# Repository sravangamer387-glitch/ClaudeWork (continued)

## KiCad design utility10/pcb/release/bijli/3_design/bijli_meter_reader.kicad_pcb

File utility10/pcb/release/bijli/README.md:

# Bijli Meter Reader - main board (rev B)

Optical electricity-meter pulse reader: USB-C 5 V powered ATmega328P-AU, sensor-head connector (phototransistor), TM1637 4-digit display connector, reset button, LED.

**Status: engineering release, software-verified only (ERC on the netlist, KiCad DRC, netlist cross-check, SPICE where noted). Not yet built, not reviewed by a second engineer, not certified.**

## Specification
- Board 52 x 38 mm, 2 layers, 1.6 mm FR-4, 1 oz copper, rounded corners R2.5 mm, 4 x M2.5 mounting holes, 2 fiducials.
- Rules used: min track 0.2 mm (power 0.4 mm), min clearance 0.2 mm, via 0.6/0.3 mm, GND pour on both layers, 39 stitching vias.
- Finish: ENIG recommended (HASL lead-free acceptable); green mask, white silk; IPC class 2.
- 23 parts, 17 nets.

## Circuit description
- **Power:** USB-C power-only sink: CC1/CC2 each 5.1 k to GND (R1, R2) so a charger delivers 5 V; 0.5 A PTC fuse F1 (1206) then +5V; SMAJ5.0A TVS D3 on VBUS clamps spikes; 10 uF + 100 nF decoupling.
- **Sensor head:** phototransistor between SIG_H and GND, 10 k pull-up R4 to +5V, 100 ohm series R6 + 100 nF C5 on SIG; SIG falls when the meter LED lights. Firmware adapts its threshold to the observed minimum/maximum (swing must be >= 0.2 V).
- **MCU/display:** ATmega328P-AU at the internal 8 MHz RC, ADC0 reads SIG, TM1637 display module on JST-PH J4 (GND, +5V, DIO, CLK), reset-bill button on PD2, LED on PD7, ISP header.

### Simulation: `sim/bijli_head_results.md`
```
| condition (phototransistor collector current) | SIG voltage | ADC counts (5 V ref) | note |
|---|---|---|---|
| dark / meter LED off, dim room (1 uA) | 4.99 V | 1021 |  |
| indoor ambient light on the head (20 uA) | 4.80 V | 982 |  |
| bright window light (150 uA) | 3.49 V | 713 |  |
| meter LED lit, weak coupling (200 uA) | 2.98 V | 610 |  |
| meter LED lit, typical close clip (1 mA) | 0.20 V | 41 | saturated (collector near 0.2 V) |
| meter LED lit, strong (3 mA) | 0.20 V | 41 | saturated (collector near 0.2 V) |

SIG = 5 V - Ic x (10 k pull-up + 100 ohm), clamped at 0.2 V (saturation). The firmware looks for a swing of more than 40 counts (0.2 V) between its running minimum and maximum, so a lit LED (>= 0.2 mA) against indoor ambient (<= 20 uA) gives a swing of more than 1.5 V. Direct sunlight on the head (> 1 mA) would hide the pulses: use the black clip. Edge speed: 10 k x 100 nF = 1 ms time constant, meter LED pulses are tens of ms.
These phototransistor currents are typical-datasheet assumptions, not measurements of a real meter.
```

## Power
MCU 5 V 8 MHz about 6 mA + display 10-30 mA + LED: under 50 mA, far below the 500 mA default USB limit and the 0.5 A PTC.

## Verification
| Check | Result |
|---|---|
| Electrical rule check on the netlist (own ERC: unconnected pins, single-pin nets, output conflicts, unpowered supplies, symbol/footprint pin match) | 0 errors, 0 warnings |
| KiCad DRC | 0 errors, 0 warnings; unconnected pads: 0 |
| Schematic netlist equals PCB netlist | yes |
| Router failures | 0 |
| 3D STEP export | yes |
| Independent Gerber parse (gerbonara): layers parsed, outline size equals the design | 9 layers, outline [52.1, 38.1] mm, match |

Enclosure (prototype shell for 3D printing): outer 67.2 x 53.2 x 21.0 mm, collision/opening check: pass

## Bill of materials
| Ref | Value | Footprint | Manufacturer part | LCSC # | LCSC status |
|---|---|---|---|---|---|
| U1 | ATmega328P-AU | TQFP-32_7x7mm_P0.8mm | ATMEGA328P-AU | C14877 | verified |
| J1 | USB-C 5V | USB_C_Receptacle_HRO_TYPE-C-31-M-12 | TYPE-C-31-M-12 | C165948 | verified |
| F1 | PTC 500mA | Fuse_1206_3216Metric | Littelfuse 1206L050YR (6 V) | C163512 | verified |
| D3 | SMAJ5.0A | D_SMA | Littelfuse SMAJ5.0A | C83329 | verified |
| J2 | ISP | PinHeader_2x03_P2.54mm_Vertical | HCTL PZ254-2-03-Z-8.5 (ZHOURI C5116479 had only 340 in stock) | C2894964 | verified |
| J3 | Sensor head | JST_PH_B3B-PH-K_1x03_P2.00mm_Vertical | JST B3B-PH-K-S(LF)(SN) | C131339 | verified |
| J4 | TM1637 display | JST_PH_B4B-PH-K_1x04_P2.00mm_Vertical | JST B4B-PH-K-S(LF)(SN) | C131334 | verified |
| SW1 | Reset bill | SW_SPST_B3U-1000P | Omron B3U-1000P | C231329 | verified |
| D1 | Green | LED_0603_1608Metric | Hubei KENTO KT-0603YG yellow-green 570 nm, Vf about 2 V (lights well from 3.3 V with 1 k; the Everlight 19-217 green was out of stock) | C2289 | verified |
| R1 | 5.1k | R_0603_1608Metric | 0603 5.1k 1% | C23186 | verified |
| R2 | 5.1k | R_0603_1608Metric | 0603 5.1k 1% | C23186 | verified |
| R3 | 10k | R_0603_1608Metric | 0603 10k 1% | C25804 | verified |
| R4 | 10k | R_0603_1608Metric | 0603 10k 1% | C25804 | verified |
| R5 | 1k | R_0603_1608Metric | 0603 1k 1% | C21190 | verified |
| R6 | 100 | R_0603_1608Metric | UNI-ROYAL 0603WAF1000T5E | C22775 | verified |
| C1 | 10u | C_0805_2012Metric | 0805 10uF X5R | C15850 | verified |
| C2 | 100n | C_0603_1608Metric | Samsung CL10B104KB8NNNC 0603 100nF X7R 50V | C1591 | verified |
| C3 | 100n | C_0603_1608Metric | Samsung CL10B104KB8NNNC 0603 100nF X7R 50V | C1591 | verified |
| C4 | 100n | C_0603_1608Metric | Samsung CL10B104KB8NNNC 0603 100nF X7R 50V | C1591 | verified |
| C5 | 100n | C_0603_1608Metric | Samsung CL10B104KB8NNNC 0603 100nF X7R 50V | C1591 | verified |
| TP1 | TP | TestPoint_Pad_D1.5mm |  |  |  |
| TP2 | TP | TestPoint_Pad_D1.5mm |  |  |  |
| TP3 | TP | TestPoint_Pad_D1.5mm |  |  |  |

`verified` = LCSC number confirmed by web search on 2026-10-31/11-01; `memory` = from my recollection, **check on lcsc.com before ordering**; empty = no number chosen (through-hole connectors, switches, buzzer, test points: hand-assembled or chosen by the buyer). `*_JLC_BOM.csv` / `*_JLC_CPL.csv` list only the parts with an LCSC number; JLCPCB rotation corrections (CPL) must be checked in their viewer.

## Assembly notes
- Reflow (JLCPCB SMT): all SMD parts with an LCSC number. Hand-solder: JST connectors, pin headers, buzzer, switches, test points as listed in the BOM. Fiducials and mounting holes are in the Gerbers.
- Polarity: LED cathode toward GND (silk marks), electrolytic none, diode D2 cathode to +V, Q2 orientation as footprint (SOT-23 pin 1 = gate).
- Programming: ISP header J2 (pin 1 = MISO, square pad). Flash the matching image from `utility10/firmware/release/`: Seeti Counter `4MHz/seeti_prod.hex` (production firmware: timer-triggered 16 kS/s ADC, scan mode to find the real whistle frequency, battery check), Rain Alert `8MHz/rain_alert.hex`, Bijli Meter Reader `8MHz/bijli_meter.hex` (demo-grade firmware, to be hardened).

## Bring-up and test
1. Plug a 5 V charger: VBUS (TP at J1/F1) = 5.0 V; +5V (TP1) = 4.9-5.0 V.
2. SIG with head disconnected = 5 V (pull-up); with the phototransistor in the dark about 4.9 V; under a lit meter LED a drop of at least 0.5 V.
3. Flash over ISP: `avrdude -p m328p -c usbasp -U lfuse:w:0xE2:m -U hfuse:w:0xD9:m -U efuse:w:0xFD:m` (internal 8 MHz, brown-out 2.7 V; USB supply is 5 V).
4. Hold the head over a 1 Hz test LED: display counts one pulse per second.

## Files
`1_fabrication/` Gerber + drill zip (upload to JLCPCB/any fab), fab notes, copper plot
`2_assembly/` JLC BOM + CPL (SMD parts JLC assembles), full BOM with LCSC numbers for every part, pick-and-place, assembly drawing
`3_design/` KiCad 7 project (pcb, schematic, libs), netlist, STEP model, schematic PDF, renders
`4_enclosure/` printable enclosure (base, screwed lid, battery door, plungers / light pipes / switch extensions) or a mounting plate for a bought IP65 box; dimensions and notes in enclosure.json
`5_verification/` DRC, ERC, verification and readiness reports

## Known limits and review checklist
- Layout was produced by a custom router and software placement; a human layout review (analog routing, ground returns, creepage, connector mechanics, silkscreen) is still required.
- Not verified: EMC, ESD (apart from TVS parts where fitted), thermal, real component tolerances, supplier stock/price, assembly house design-for-manufacture check (run JLCPCB's DFM check on the Gerbers).
- Firmware thresholds are placeholders to be calibrated on prototypes.

## Manufacturing readiness (automatic check)

| Check | Result |
|---|---|
| gerber layers and drill present | PASS |
| drc errors 0 | PASS |
| unconnected 0 | PASS |
| netlist matches schematic | PASS |
| erc errors 0 | PASS |
| independent gerber check clean | PASS |
| every part has lcsc number | PASS |
| every lcsc number verified | PASS |
| cpl rows equal jlc bom parts | PASS |
| step model | PASS |
| KiCad DRC warnings | 0 |
| **Order ready** | **YES** |

Order steps: (1) upload `1_fabrication/*_gerbers.zip`; (2) for assembly upload `2_assembly/*_JLC_BOM.csv` and `*_JLC_CPL.csv`, check the 3D/rotation preview for every polarised part (diodes, ICs, LEDs, electrolytics) because CPL rotations are generated, not hand-checked; (3) buy the through-hole parts listed in `*_BOM_full.csv` marked hand/THT and solder them; (4) re-check stock and the exact LCSC listing for every line before paying.

Limits: the layout is software-generated and has not been reviewed by a PCB engineer; no prototype has been built; the first batch should be treated as a prototype run (order 5 boards).

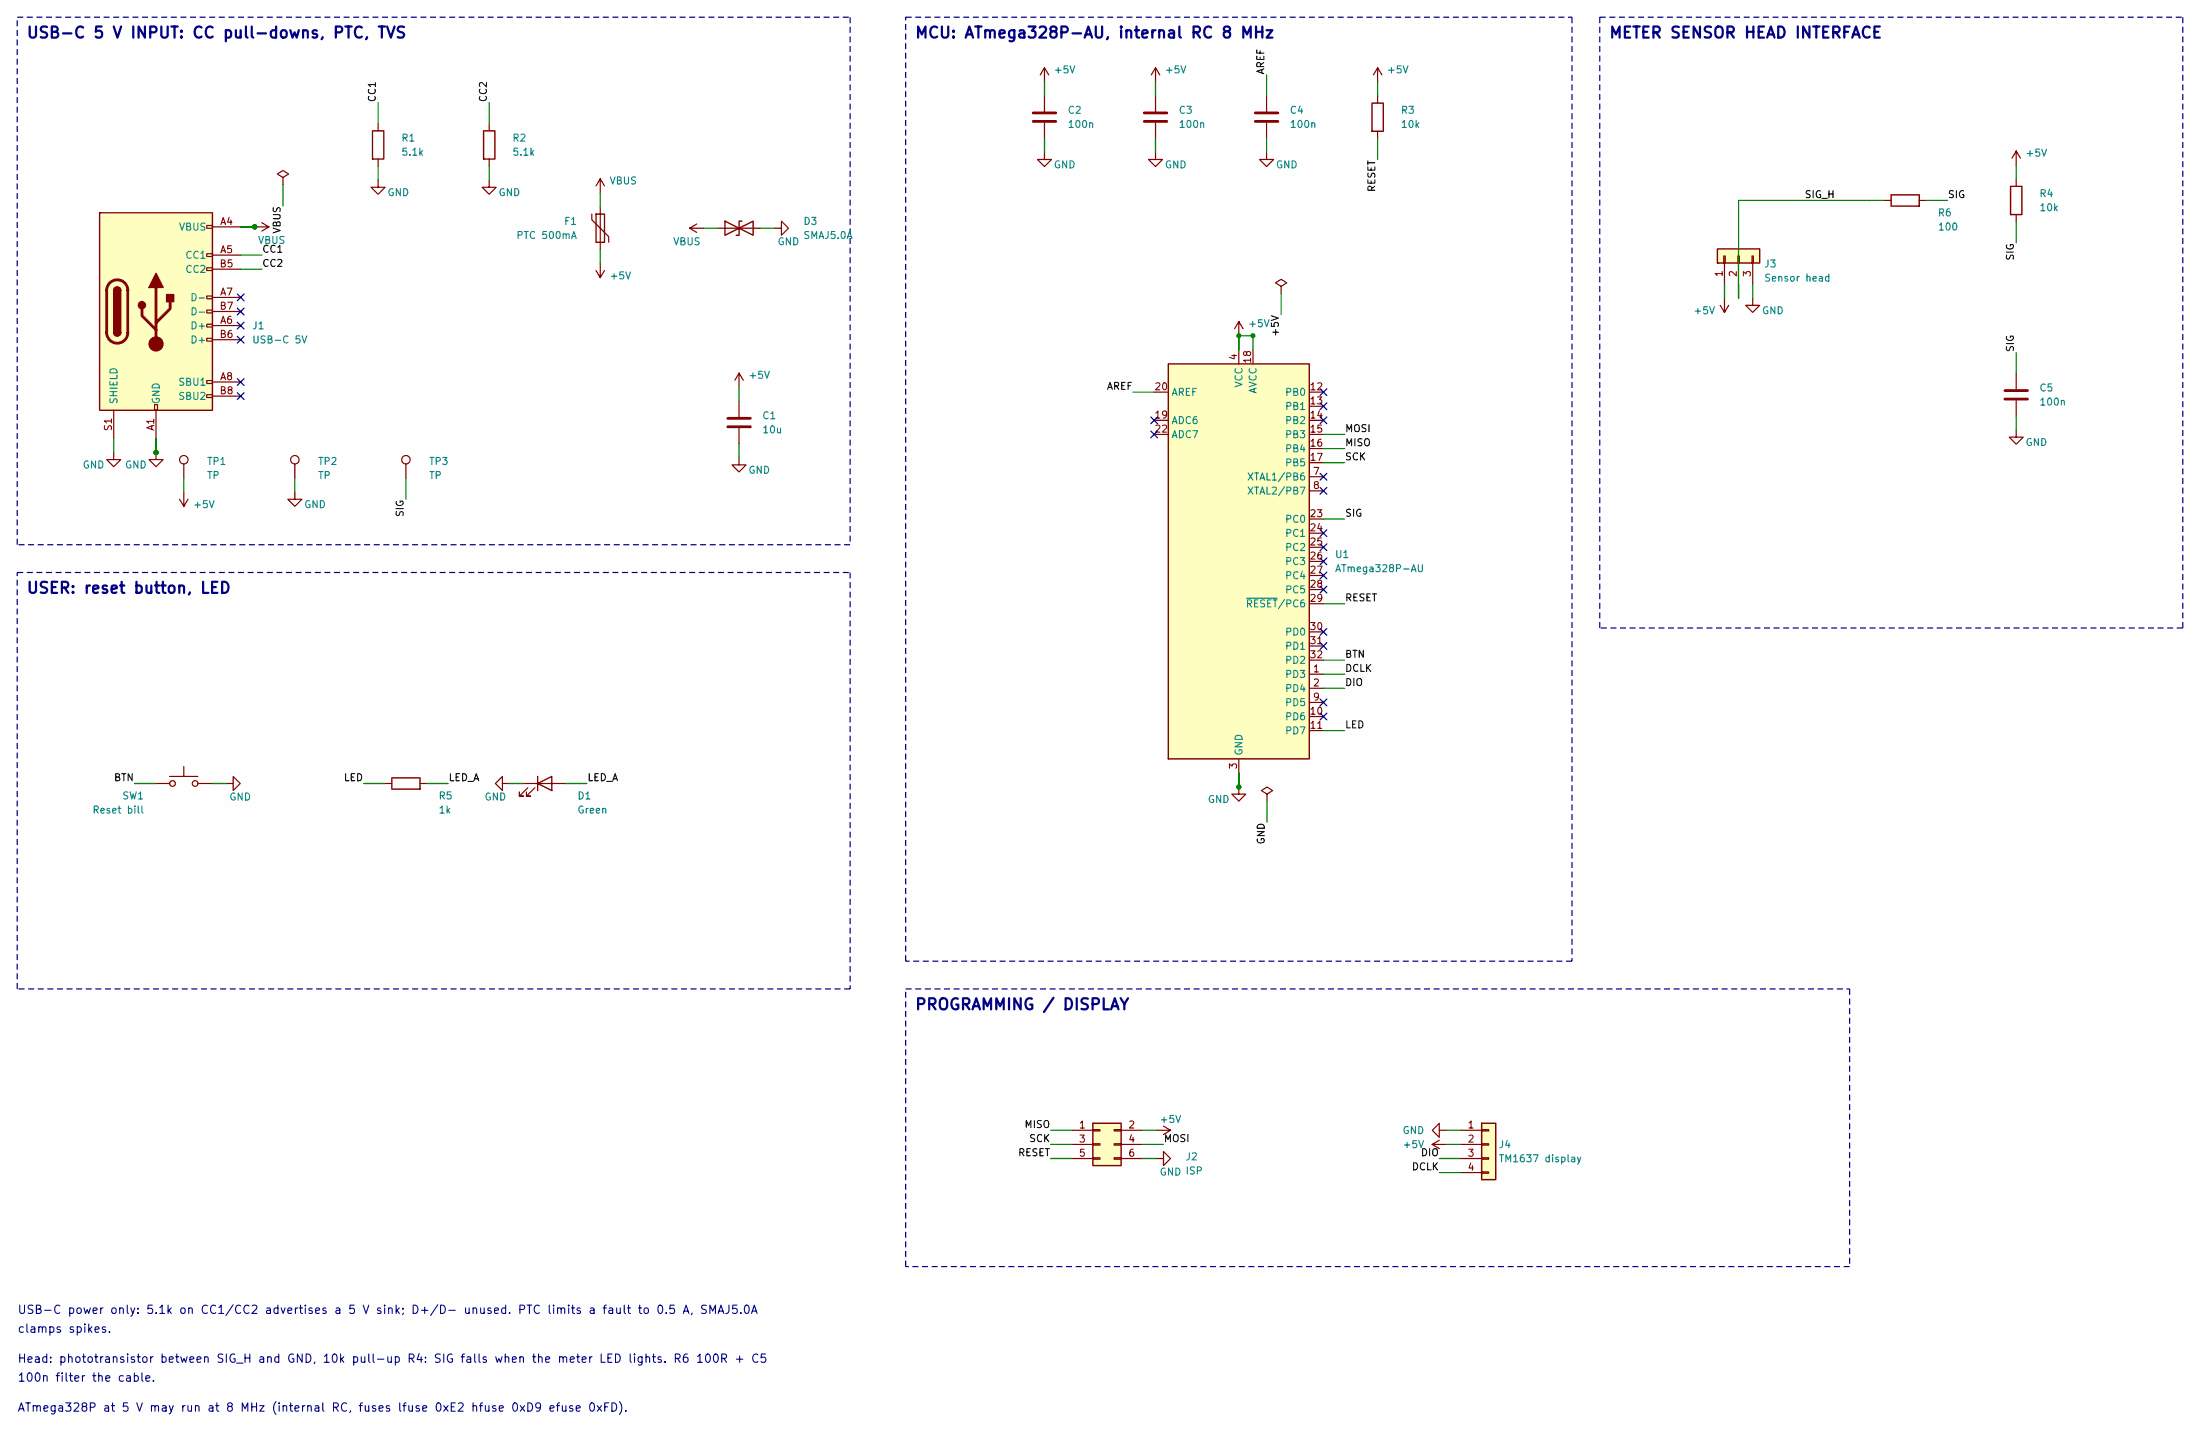
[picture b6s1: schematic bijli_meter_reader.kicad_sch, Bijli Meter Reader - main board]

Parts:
C1: 10u; C_0805_2012Metric
C2, C3, C4, C5: 100n; C_0603_1608Metric
D1: Green; LED_0603_1608Metric
D3: SMAJ5.0A; D_SMA
F1: PTC 500mA; Fuse_1206_3216Metric
J1: USB-C 5V; USB_C_Receptacle_HRO_TYPE-C-31-M-12
J2: ISP; PinHeader_2x03_P2.54mm_Vertical
J3: Sensor head; JST_PH_B3B-PH-K_1x03_P2.00mm_Vertical
J4: TM1637 display; JST_PH_B4B-PH-K_1x04_P2.00mm_Vertical
R1, R2: 5.1k; R_0603_1608Metric
R3, R4: 10k; R_0603_1608Metric
R5: 1k; R_0603_1608Metric
R6: 100; R_0603_1608Metric
SW1: Reset bill; SW_SPST_B3U-1000P
TP1, TP2, TP3: TP; TestPoint_Pad_D1.5mm
U1: ATmega328P-AU; TQFP-32_7x7mm_P0.8mm

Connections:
+5V: C1.1, C2.1, C3.1, F1.2, J2.2, J3.1, J4.2, R3.1, R4.1, TP1.1, U1.4 (VCC), U1.6 (VCC), U1.18 (AVCC)
AREF: C4.1, U1.20 (AREF)
BTN: SW1.1, U1.32 (PD2)
CC1: J1.A5 (CC1), R1.1
CC2: J1.B5 (CC2), R2.1
DCLK: J4.4, U1.1 (PD3)
DIO: J4.3, U1.2 (PD4)
GND: C1.2, C2.2, C3.2, C4.2, C5.2, D1.1 (K), D3.2 (A2), J1.A1 (GND), J1.A12 (GND), J1.B1 (GND), J1.B12 (GND), J1.S1 (SHIELD), J2.6, J3.3, J4.1, R1.2, R2.2, SW1.2, TP2.1, U1.3 (GND), U1.5 (GND), U1.21 (GND)
LED: R5.1, U1.11 (PD7)
LED_A: D1.2 (A), R5.2
MISO: J2.1, U1.16 (PB4)
MOSI: J2.4, U1.15 (PB3)
RESET: J2.5, R3.2, U1.29 (~RESET/PC6)
SCK: J2.3, U1.17 (PB5)
SIG: C5.1, R4.2, R6.2, TP3.1, U1.23 (PC0)
SIG_H: J3.2, R6.1
VBUS: D3.1 (A1), F1.1, J1.A4 (VBUS), J1.A9 (VBUS), J1.B4 (VBUS), J1.B9 (VBUS)

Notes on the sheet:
USB-C 5 V INPUT: CC pull-downs, PTC, TVS
MCU: ATmega328P-AU, internal RC 8 MHz
USER: reset button, LED
METER SENSOR HEAD INTERFACE
PROGRAMMING / DISPLAY
USB-C power only: 5.1k on CC1/CC2 advertises a 5 V sink; D+/D- unused. PTC limits a fault to 0.5 A, SMAJ5.0A
clamps spikes.
Head: phototransistor between SIG_H and GND, 10k pull-up R4: SIG falls when the meter LED lights. R6 100R + C5
100n filter the cable.
ATmega328P at 5 V may run at 8 MHz (internal RC, fuses lfuse 0xE2 hfuse 0xD9 efuse 0xFD).

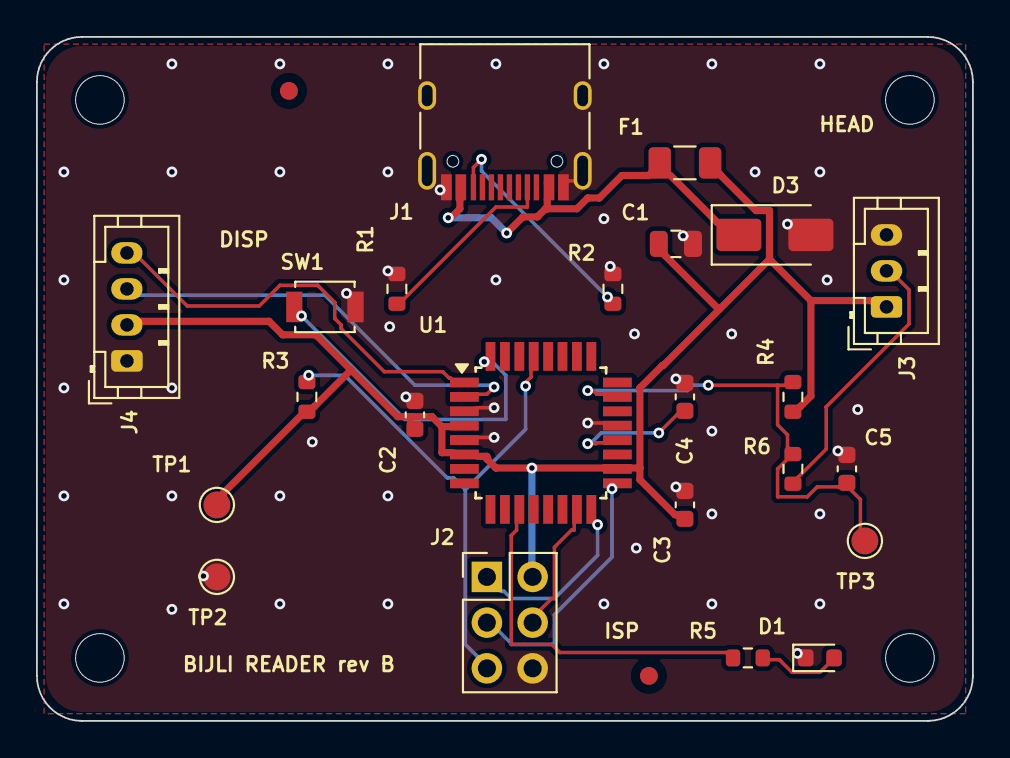
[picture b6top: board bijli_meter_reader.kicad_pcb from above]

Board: 2 copper layers, 52.0 x 38.0 mm, 29 parts (0 on the bottom side), 17 nets.

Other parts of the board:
FID1, FID2: Fiducial; Fiducial_1mm_Mask2mm
H1, H2, H3, H4: M2.5; MountingHole_2.7mm_M2.5
